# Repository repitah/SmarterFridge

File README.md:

# SmarterFridge
Digital (AVR MCU) replacement for fridge analogue thermistat.
Circuit is essentially a custom Arduino with ATMEGA328P.

This is one of my first "major" projects (circa 2012), and a lot has been learnt since then.

Additional features (because why not)
* Fan to circulate air over the cooling radiator
  * Does not run the fan when the door is open
  * Gives an old and basic fridge more modern and expensive features.
* Door open/ajar reminder (buzzer)
* Anti-freeze / defroster (since the old fridge was a "frost-free" type.
* Does not start the compressor until the door is closed

Project notes:
* Circuit and PCB done with EagleCAD -- Only learnt basic KiCAD in a later project.
* Done with Code::Blocks (painful setup, but I wanted a half decent IDE. It should convert back to Arduno IDE fairly easily.
* In hindsight:
  * Software: not using the default Arduino bootloader may be better (doesn't pulse the pins on boot); (OptiBoot?)
  * Hardware: drive the transistors, from the MCU, via a resistor and have a pulldown
  * Hardware: There are nice modular 110V/220V mains to 12V modules that could shrink the total install package size.
  * Hardware: add simple debounce circuit to door switch. Maybe even a gated debounce.
  * Hardware: The fan turned out to be annoying in terms of humming sound. With a differnt type of fan and a custom 3D printed baffle, the idea could be promissing.
  * Hardware: Maybe port to a more modern cheap platform (ESP8266/ESP32) and/or surface mount components

Background story:
The fridge I got when I moved in to my first apartment was an old 80's/90's model that had been working reasonably well for the 5 years before this project was dreamed up. The driving reasons for this projects was: the replacement analogue thermistat was expensive; I had an interest in electronics for most of my life and had a dangerously primative knowledge of circuit (inspite of doing a few subjects in university); Arduinos were all the rage; I wanted to learn and most of the fancy fridges had some MCU type setup. Above all, the over-running of the compressor was costing me a small fortune in electricity and spoiling my fresh fruit and veg... it had to be fixed... I wanted to learn... I wasn't spending a small fortunate buying a new fridge because of 1 bad part.

My then partner, being a freshly minted professional programmer, helped me setup Code::Blocks as I wanted an IDE more akin to Visual Studio, or at least better than the basic notepad like setup that shipped for the Arduino back then (early 2010's).

The project was fun, learning about NTC resistors, voltage dividers, and even how to do lithography and make a PCB with cheap pool acid. It was also an introduction to HVAC to me -- something useful later in my career.

Sadly, 4 years later, I got home one warm summer evening and found the fridge had given up on me (I suspect a refridgerant leak, causing overheat/failure of the compressor) and was replaced with another basic fridge with analogue thermistat, the very next day -- and so this project may still be useful to necro at some point.

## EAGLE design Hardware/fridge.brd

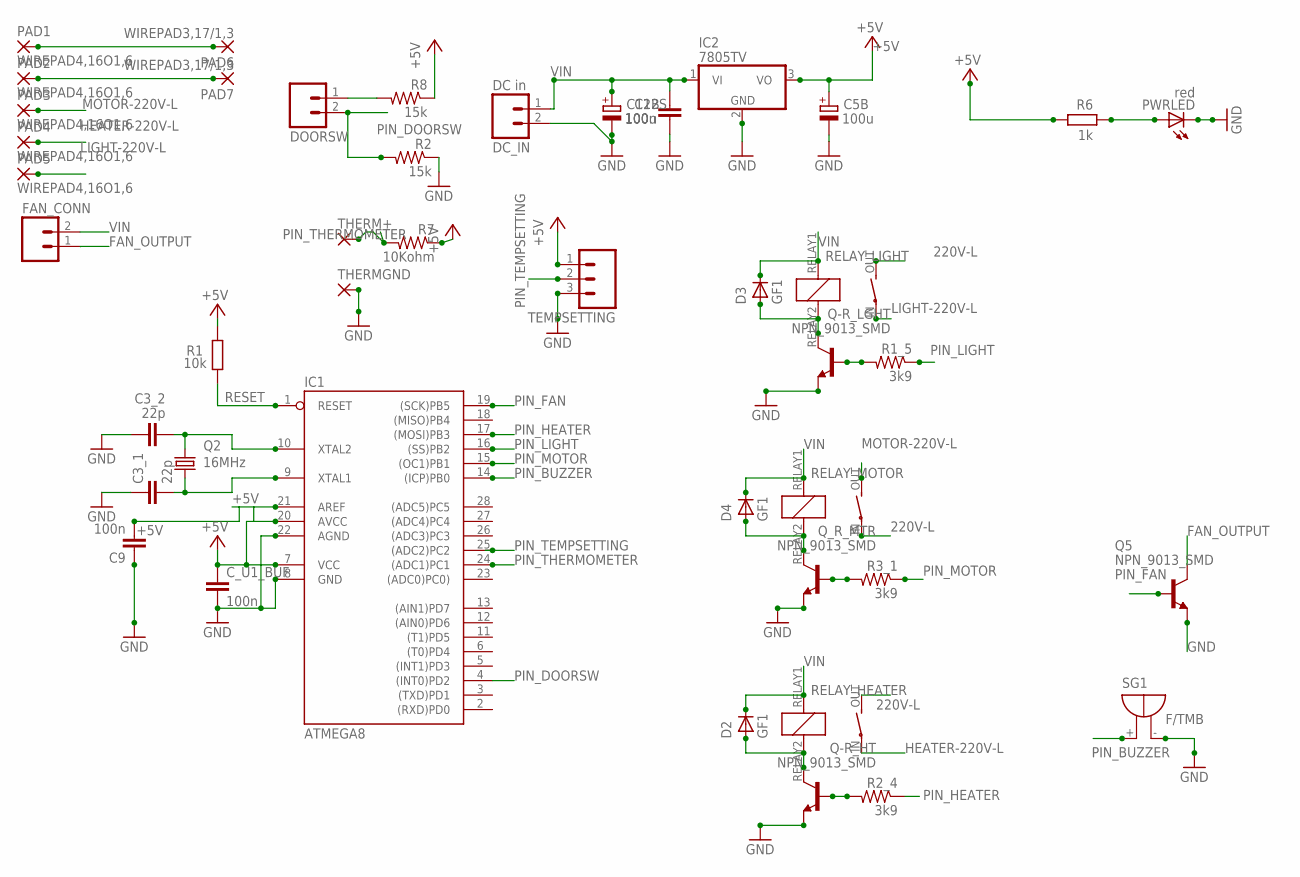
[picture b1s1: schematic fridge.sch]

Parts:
C3_1, C3_2: 22p; C025-025X050
C5B, C12B: 100u; E2,5-7
C9: 100n; C050-030X075
C12S: 100n; C050-035X075
C_U1_BUF: 100n; C050-035X075
D2, D3, D4: GF1; SMA-DO214AC
DC_IN: DC in; 02P
DOORSW: M02; 02P
FAN_CONN: M02; 02P
IC1: ATMEGA8; DIL28-3
IC2: 7805TV; TO220V
PAD1, PAD2, PAD3, PAD4, PAD5: WIREPAD4,16O1,6; 4,16O1,6
PAD6, PAD7: WIREPAD3,17/1,3; 3,17/1,3
PWRLED: red; LED5MM
Q2: 16MHz; HC49/S
Q5: NPN_9013_SMD; TO92
Q-R_HT: NPN_9013_SMD; TO92
Q-R_LGHT: NPN_9013_SMD; TO92
Q_R_MTR: NPN_9013_SMD; TO92
R1: 10k; 0204/7
R1_5, R2_4, R3_1: 3k9; 0204/7
R2, R8: 15k; 0204V
R6: 1k; 0204/7
R7: 10Kohm; 0204V
RELAY_HEATER: OJE-SS-112HMFSPSTOJE-SS-112HMF; OJ/OJE_SERIES
RELAY_LIGHT: OJE-SS-112HMFSPSTOJE-SS-112HMF; OJ/OJE_SERIES
RELAY_MOTOR: OJE-SS-112HMFSPSTOJE-SS-112HMF; OJ/OJE_SERIES
SG1: F/TMB
TEMPSETTING: M03; 03P
THERM+: 1,6/0,9
THERMGND: 1,6/0,9

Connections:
220V-L: PAD1.1, PAD6.1, RELAY_HEATER.OUT, RELAY_LIGHT.OUT, RELAY_MOTOR.IN
220V-N: PAD2.1, PAD7.1
+5V: C5B.+, C9.2, C_U1_BUF.1, IC1.7 (VCC), IC1.20 (AVCC), IC1.21 (AREF), IC2.3 (VO), R1.2, R6.1, R7.1, R8.1, TEMPSETTING.1
FAN_OUTPUT: FAN_CONN.1, Q5.3 (C)
GND: C3_1.1, C3_2.1, C5B.-, C9.1, C12B.-, C12S.1, C_U1_BUF.2, DC_IN.2, IC1.8 (GND), IC1.22 (AGND), IC2.2 (GND), PWRLED.K (C), Q5.1 (E), Q-R_HT.1 (E), Q-R_LGHT.1 (E), Q_R_MTR.1 (E), R2.1, SG1.-, TEMPSETTING.3, THERMGND.1
HEATER-220V-L: PAD4.1, RELAY_HEATER.IN
LIGHT-220V-L: PAD5.1, RELAY_LIGHT.IN
MOTOR-220V-L: PAD3.1, RELAY_MOTOR.OUT
unnamed: DOORSW.1, R8.2
unnamed: Q-R_HT.2 (B), R2_4.2
unnamed: PWRLED.A, R6.2
unnamed: D2.A, Q-R_HT.3 (C), RELAY_HEATER.RELAY2 (RELAY_2)
unnamed: Q-R_LGHT.2 (B), R1_5.2
unnamed: C3_1.2, IC1.9 (XTAL1), Q2.1
unnamed: C3_2.2, IC1.10 (XTAL2), Q2.2
unnamed: D4.A, Q_R_MTR.3 (C), RELAY_MOTOR.RELAY2 (RELAY_2)
unnamed: Q_R_MTR.2 (B), R3_1.2
unnamed: D3.A, Q-R_LGHT.3 (C), RELAY_LIGHT.RELAY2 (RELAY_2)
PIN_BUZZER: IC1.14 ((ICP)PB0), SG1.+
PIN_DOORSW: DOORSW.2, IC1.4 ((INT0)PD2), R2.2
PIN_FAN: IC1.19 ((SCK)PB5), Q5.2 (B)
PIN_HEATER: IC1.17 ((MOSI)PB3), R2_4.1
PIN_LIGHT: IC1.16 ((SS)PB2), R1_5.1
PIN_MOTOR: IC1.15 ((OC1)PB1), R3_1.1
PIN_TEMPSETTING: IC1.25 ((ADC2)PC2), TEMPSETTING.2
PIN_THERMOMETER: IC1.24 ((ADC1)PC1), R7.2, THERM+.1
RESET: IC1.1 (RESET), R1.1
VIN: C12B.+, C12S.2, D2.K (C), D3.K (C), D4.K (C), DC_IN.1, FAN_CONN.2, IC2.1 (VI), RELAY_HEATER.RELAY1 (RELAY_1), RELAY_LIGHT.RELAY1 (RELAY_1), RELAY_MOTOR.RELAY1 (RELAY_1)

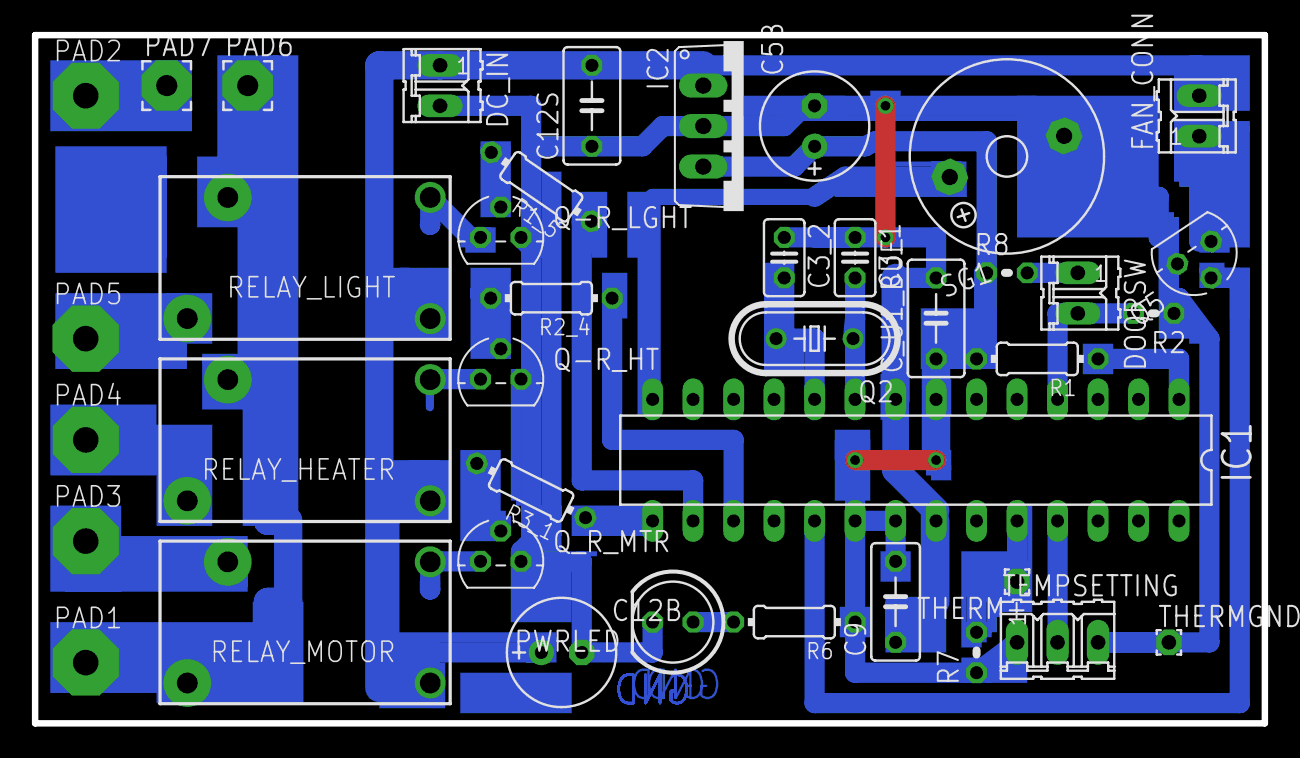
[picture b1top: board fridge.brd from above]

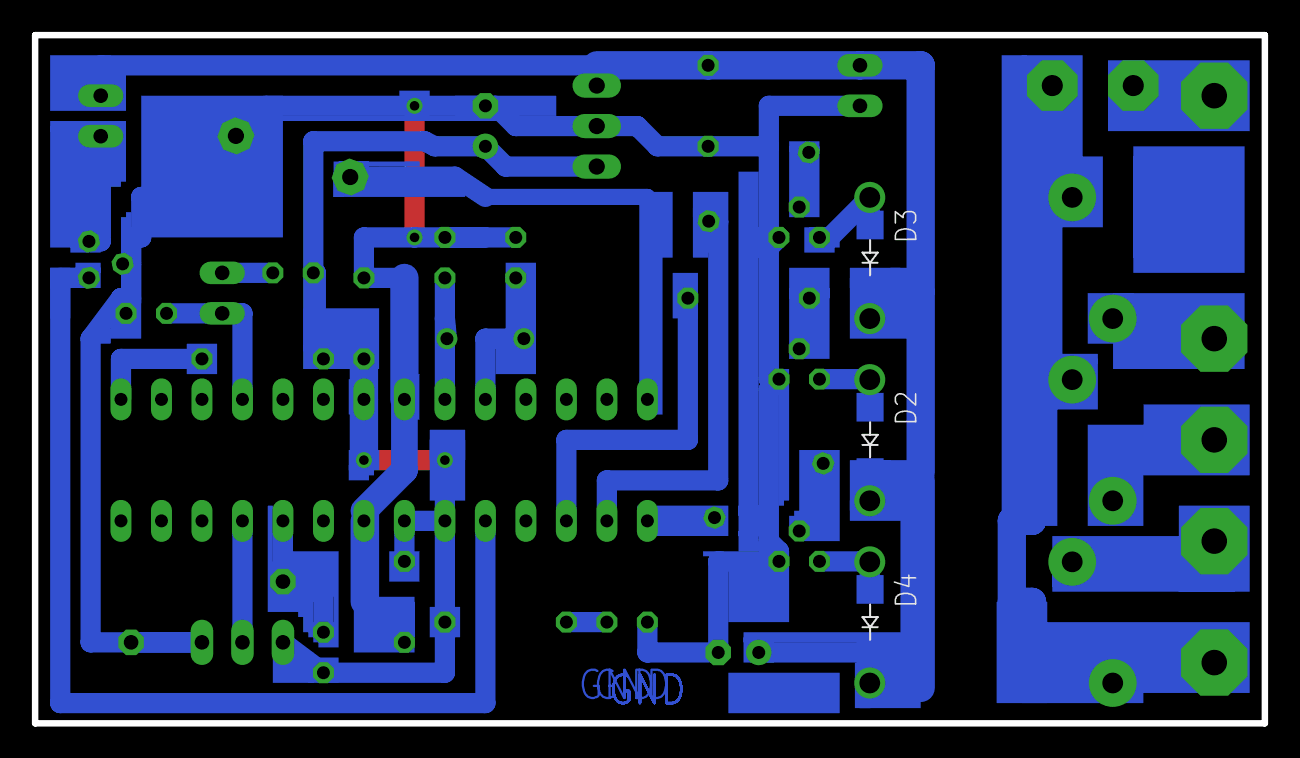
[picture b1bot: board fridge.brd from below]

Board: 2 copper layers, 77.1 x 43.2 mm, 43 parts (3 on the bottom side), 28 nets.

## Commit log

2019-08-24 Initial software code commit
2019-08-24 Initial hardware dump
2019-08-24 Original PCB Layout
2019-08-24 Additional proof of work
